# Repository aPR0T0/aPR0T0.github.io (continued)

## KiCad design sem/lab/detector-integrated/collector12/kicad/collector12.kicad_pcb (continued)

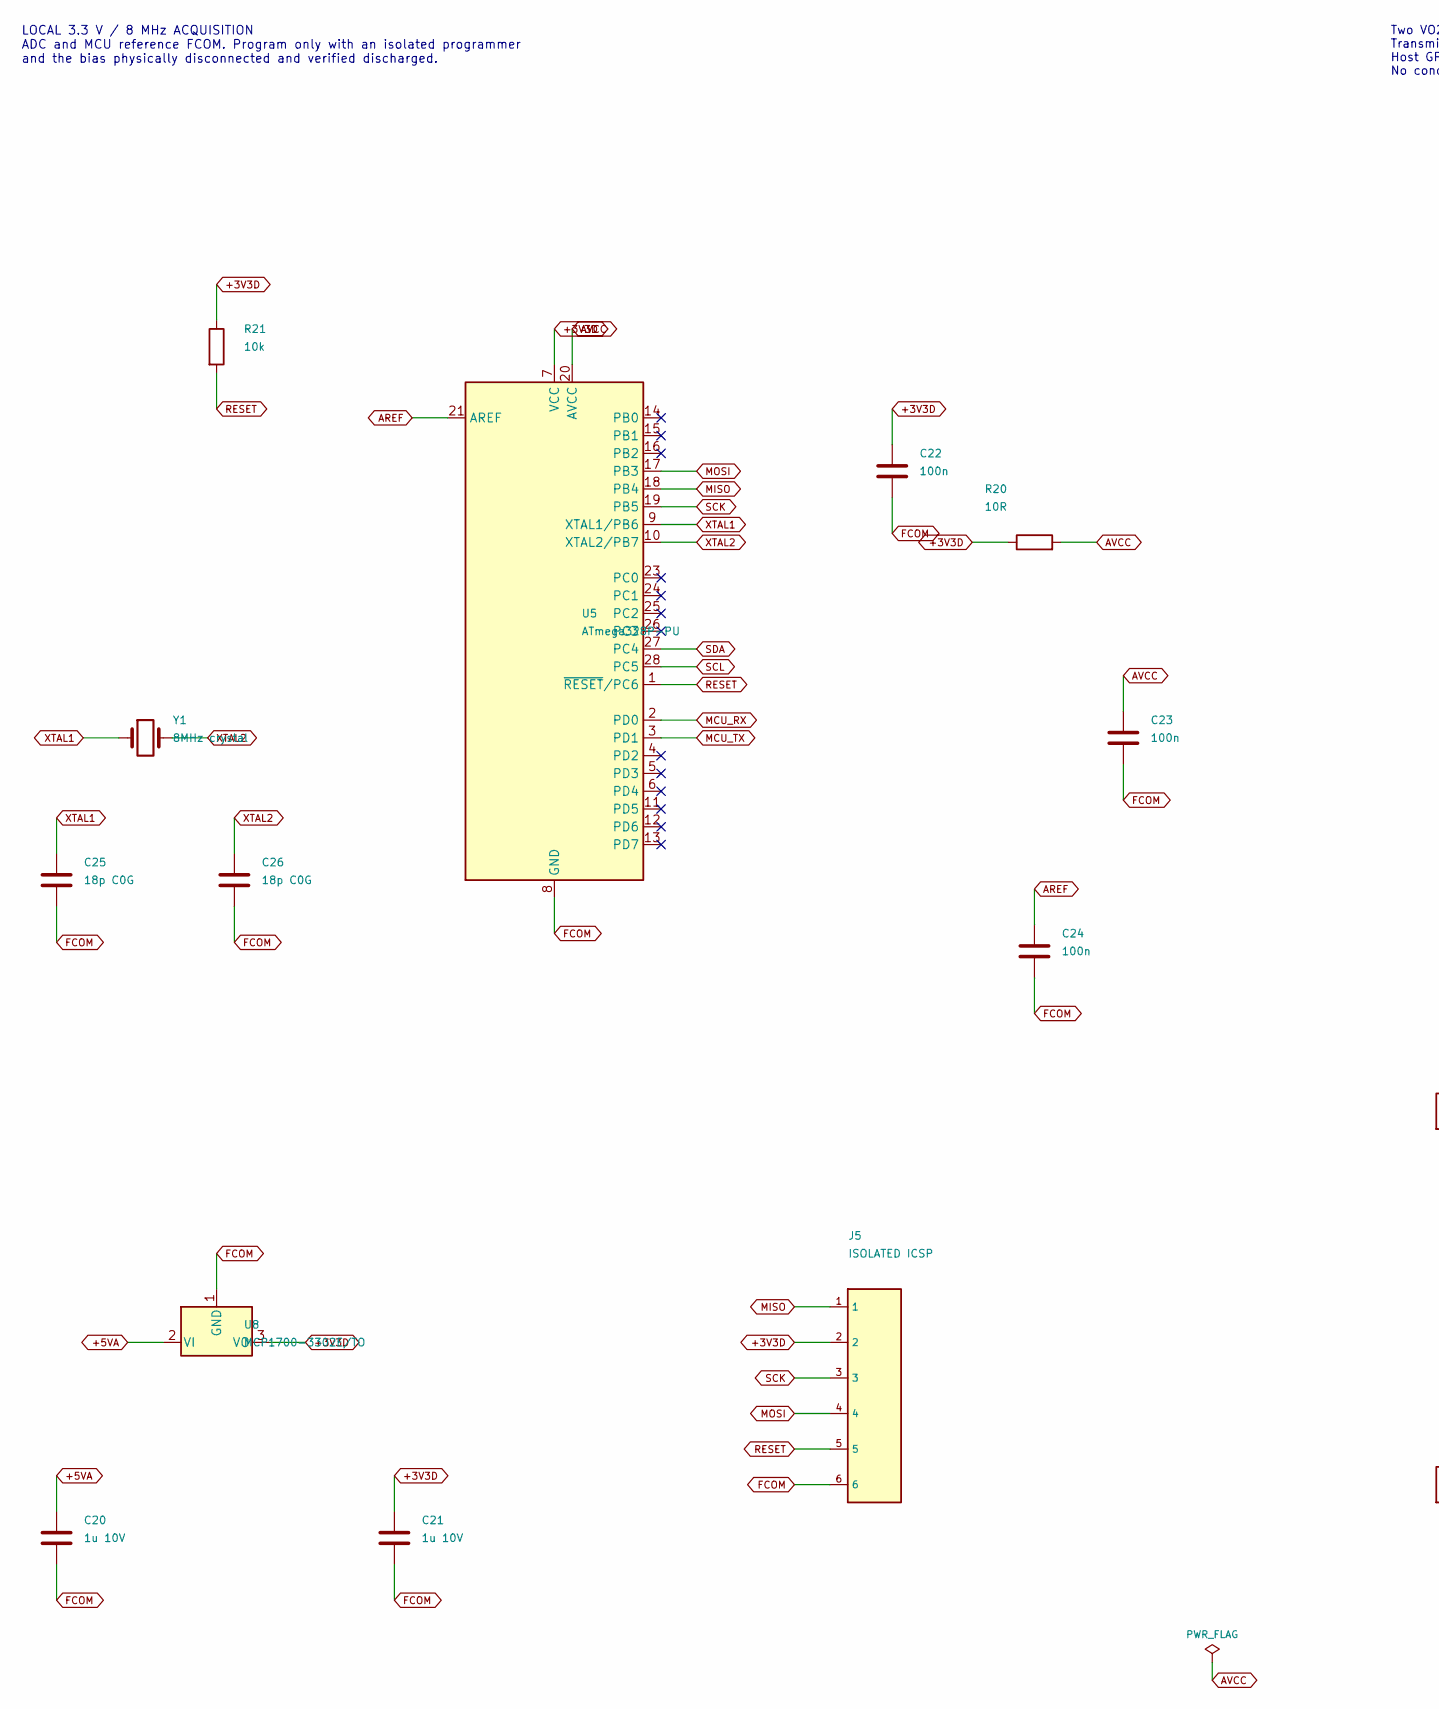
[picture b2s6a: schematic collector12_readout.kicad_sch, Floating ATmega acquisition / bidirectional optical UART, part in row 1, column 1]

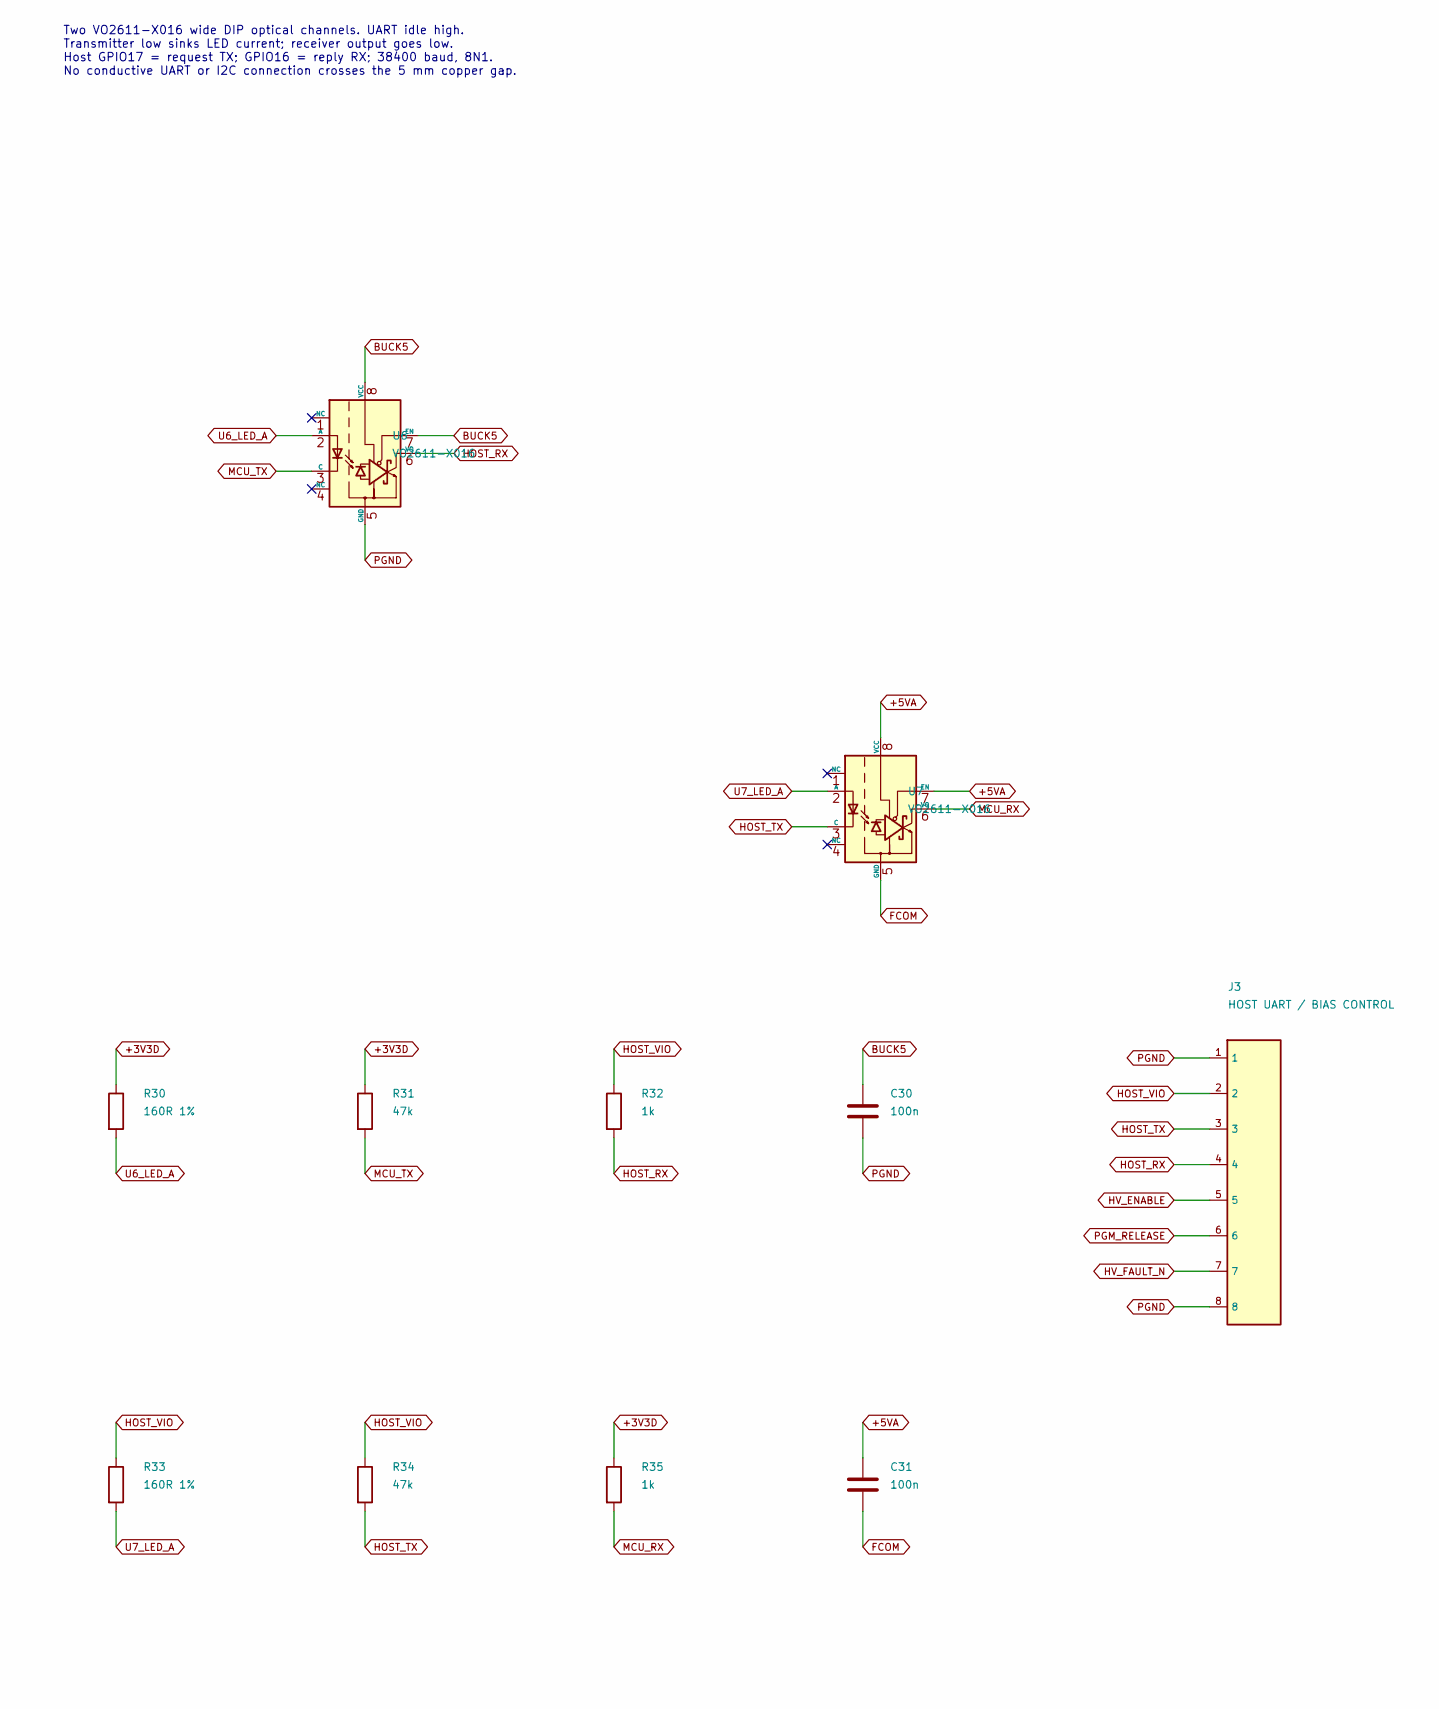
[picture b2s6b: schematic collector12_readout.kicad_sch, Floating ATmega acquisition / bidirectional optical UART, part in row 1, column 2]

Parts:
C20, C21: 1u 10V; C_0805_2012Metric
C22, C23, C24, C30, C31: 100n; C_0805_2012Metric
C25, C26: 18p C0G; C_0805_2012Metric
J3: HOST UART / BIAS CONTROL; PinHeader_1x08_P2.54mm_Vertical
J5: ISOLATED ICSP; PinHeader_2x03_P2.54mm_Vertical
R20: 10R; R_0805_2012Metric
R21: 10k; R_0805_2012Metric
R30, R33: 160R 1%; R_0805_2012Metric
R31, R34: 47k; R_0805_2012Metric
R32, R35: 1k; R_0805_2012Metric
U5: ATmega328P-PU; DIP-28_W7.62mm; MPN ATmega328P-PU
U6, U7: VO2611-X016; DIP-8_W10.16mm; MPN VO2611-X016
U8: MCP1700-3302E/TO; TO-92_Inline; MPN MCP1700-3302E/TO
Y1: 8MHz crystal; Crystal_HC49-U_Vertical

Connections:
+3V3D: C21.1, C22.1, J5.2, R20.1, R21.1, R30.1, R31.1, R35.1, U5.7 (VCC), U8.3 (VO)
+5VA: C20.1, C31.1, U7.7 (EN), U7.8 (VCC), U8.2 (VI); also elsewhere on the board
AREF: C24.1, U5.21 (AREF)
AVCC: C23.1, R20.2, U5.20 (AVCC)
BUCK5: C30.1, U6.7 (EN), U6.8 (VCC); also elsewhere on the board
FCOM: C20.2, C21.2, C22.2, C23.2, C24.2, C25.2, C26.2, C31.2, J5.6, U5.8 (GND), U5.22 (GND), U7.5 (GND), U8.1 (GND); also elsewhere on the board
HOST_RX: J3.4, R32.2, U6.6 (VO)
HOST_TX: J3.3, R34.2, U7.3 (C)
HOST_VIO: J3.2, R32.1, R33.1, R34.1; also elsewhere on the board
HV_ENABLE: J3.5; also elsewhere on the board
HV_FAULT_N: J3.7; also elsewhere on the board
MCU_RX: R35.2, U5.2 (PD0), U7.6 (VO)
MCU_TX: R31.2, U5.3 (PD1), U6.3 (C)
MISO: J5.1, U5.18 (PB4)
MOSI: J5.4, U5.17 (PB3)
PGM_RELEASE: J3.6; also elsewhere on the board
PGND: C30.2, J3.1, J3.8, U6.5 (GND); also elsewhere on the board
RESET: J5.5, R21.2, U5.1 (~RESET/PC6)
SCK: J5.3, U5.19 (PB5)
SCL: U5.28 (PC5); also elsewhere on the board
SDA: U5.27 (PC4); also elsewhere on the board
U6_LED_A: R30.2, U6.2 (A)
U7_LED_A: R33.2, U7.2 (A)
XTAL1: C25.1, U5.9 (XTAL1/PB6), Y1.1
XTAL2: C26.1, U5.10 (XTAL2/PB7), Y1.2

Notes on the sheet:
LOCAL 3.3 V / 8 MHz ACQUISITION ADC and MCU reference FCOM. Program only with an isolated programmer and the bias physically disconnected and verified discharged.
Two VO2611-X016 wide DIP optical channels. UART idle high. Transmitter low sinks LED current; receiver output goes low. Host GPIO17 = request TX; GPIO16 = reply RX; 38400 baud, 8N1. No conductive UART or I2C connection crosses the 5 mm copper gap.

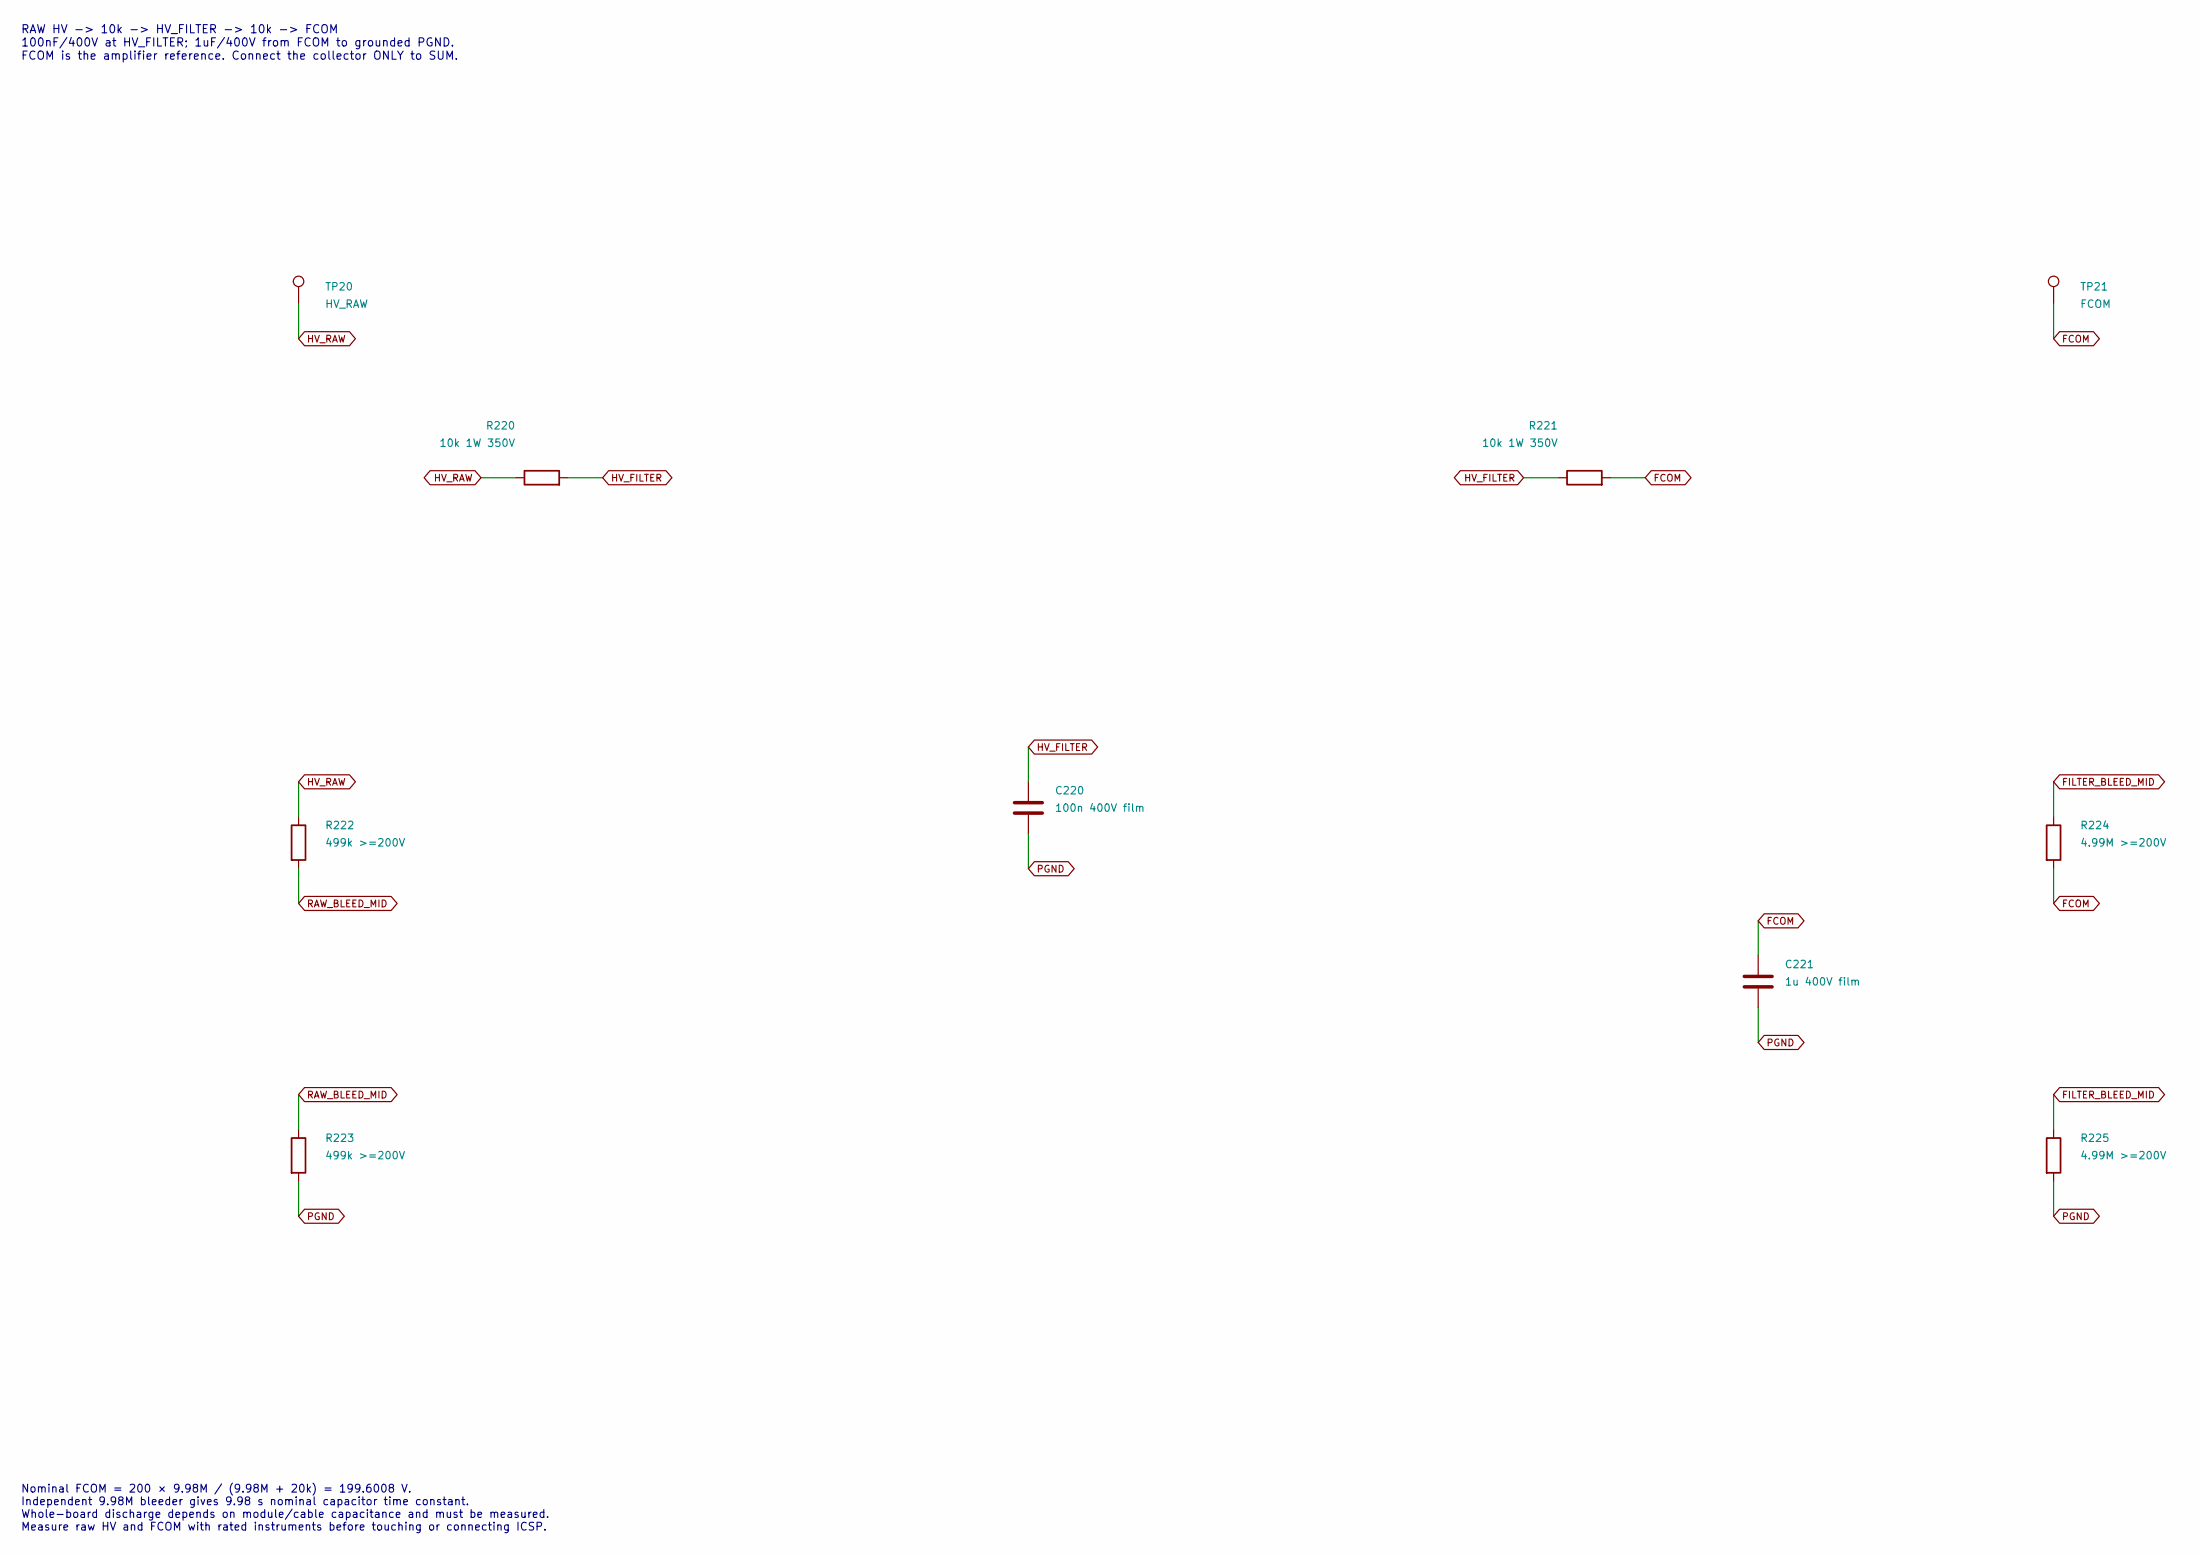
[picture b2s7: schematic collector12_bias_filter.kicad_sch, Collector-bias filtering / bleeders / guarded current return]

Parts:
C220: 100n 400V film; C_Rect_L13.0mm_W5.0mm_P10.00mm_FKS3_FKP3_MKS4
C221: 1u 400V film; C_Rect_L29.0mm_W11.9mm_P27.50mm_MKT
R220, R221: 10k 1W 350V; PR01_P10.16; MPN PR01000101002FA100
R222, R223: 499k >=200V; PR01_P10.16
R224, R225: 4.99M >=200V; PR01_P10.16
TP20: HV_RAW; TestPoint_THTPad_D2.0mm_Drill1.0mm
TP21: FCOM; TestPoint_THTPad_D2.0mm_Drill1.0mm

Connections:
FCOM: C221.1, R221.2, R224.2, TP21.1; also elsewhere on the board
FILTER_BLEED_MID: R224.1, R225.1
HV_FILTER: C220.1, R220.2, R221.1
HV_RAW: R220.1, R222.1, TP20.1; also elsewhere on the board
PGND: C220.2, C221.2, R223.2, R225.2; also elsewhere on the board
RAW_BLEED_MID: R222.2, R223.1

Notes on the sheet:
RAW HV -> 10k -> HV_FILTER -> 10k -> FCOM 100nF/400V at HV_FILTER; 1uF/400V from FCOM to grounded PGND. FCOM is the amplifier reference. Connect the collector ONLY to SUM.
Nominal FCOM = 200 × 9.98M / (9.98M + 20k) = 199.6008 V. Independent 9.98M bleeder gives 9.98 s nominal capacitor time constant. Whole-board discharge depends on module/cable capacitance and must be measured. Measure raw HV and FCOM with rated instruments before touching or connecting ICSP.

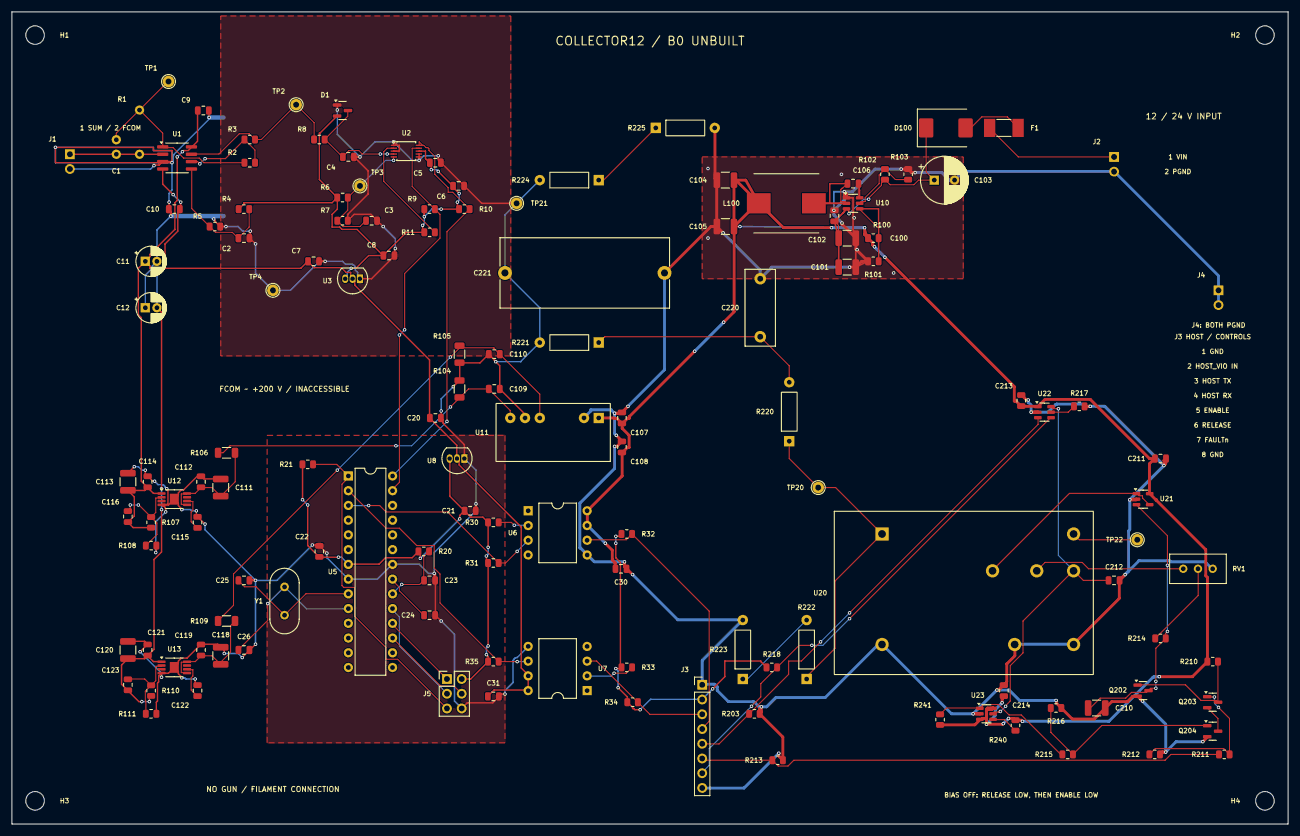
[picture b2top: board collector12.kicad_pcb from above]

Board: 2 copper layers, 220.0 x 140.0 mm, 140 parts (0 on the bottom side), 67 nets.

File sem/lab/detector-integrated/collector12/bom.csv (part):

Reference,Value,Quantity,MPN_or_procurement_spec,Footprint,Function,Datasheet
U1,LMC662AIM,1,LMC662AIMX/NOPB,Package_SO:SOIC-8_3.9x4.9mm_P1.27mm,"Dual CMOS TIA / attenuator; solder directly, no socket",https://www.ti.com/lit/ds/symlink/lmc662.pdf
R1,100M 1%,1,HVA05FA100M,Resistor_THT:R_Axial_DIN0207_L6.3mm_D2.5mm_P7.62mm_Horizontal,100M axial 6x2.5mm body; tolerance calibrates,
C1,10p C0G,1,10p C0G,Capacitor_THT:C_Disc_D3.0mm_W1.6mm_P2.50mm,"TIA stability, tau=1ms nominal; real input capacitance must be tested",
J1,COLLECTOR / FCOM,1,COLLECTOR / FCOM,Connector_PinHeader_2.54mm:PinHeader_1x02_P2.54mm_Vertical,"1 collector, 2 inner guard at FCOM; outer shield to J4 chamber ground",
R2,40.2k 0.1%,1,40.2k 0.1%,Resistor_SMD:R_0805_2012Metric,Attenuator input,
R3,10.0k 0.1%,1,10.0k 0.1%,Resistor_SMD:R_0805_2012Metric,Attenuator feedback,
R4,15.0k 0.1%,1,15.0k 0.1%,Resistor_SMD:R_0805_2012Metric,VBIAS upper divider,
R5,10.0k 0.1%,1,10.0k 0.1%,Resistor_SMD:R_0805_2012Metric,VBIAS lower divider,
C2,1u 10V X7R,1,1u 10V X7R,Capacitor_SMD:C_0805_2012Metric,Quiet 1.32V filter,
R6,1.00k 0.1%,1,1.00k 0.1%,Resistor_SMD:R_0805_2012Metric,ADC midpoint divider upper / rail bleeder,
R7,1.00k 0.1%,1,1.00k 0.1%,Resistor_SMD:R_0805_2012Metric,ADC midpoint divider lower,
C3,10u 10V X7R,1,10u 10V X7R,Capacitor_SMD:C_0805_2012Metric,1.65V reference filter,
R8,820R,1,820R,Resistor_SMD:R_0805_2012Metric,ADC overload current limit; downstream of sensitive node,
C4,100n,1,100n,Capacitor_SMD:C_0805_2012Metric,ADC local RC filter,
D1,BAT54S,1,BAT54S,Package_TO_SOT_SMD:SOT-23,ADC-only Schottky clamp; never on SUM,https://assets.nexperia.com/documents/data-sheet/BAT54S.pdf
U2,ADS1115IDGS,1,ADS1115IDGSR,Package_SO:TSSOP-10_3x3mm_P0.5mm,Differential AIN0-AIN1; I2C0x48; PGA +/-256mV 128SPS defaults,https://www.ti.com/lit/ds/symlink/ads1115.pdf
R9,4.7k,1,4.7k,Resistor_SMD:R_0805_2012Metric,I2C pull-up,
R10,4.7k,1,4.7k,Resistor_SMD:R_0805_2012Metric,I2C pull-up,
R11,10k,1,10k,Resistor_SMD:R_0805_2012Metric,Optional ready open-drain pull-up,
C5,100n,1,100n,Capacitor_SMD:C_0805_2012Metric,ADC local bypass,
C6,1u 10V,1,1u 10V,Capacitor_SMD:C_0805_2012Metric,ADC local bulk bypass,
U3,MCP1700-3302E/TO,1,MCP1700-3302E/TO,Package_TO_SOT_THT:TO-92_Inline,3.3V ADC supply derived from +5V; max input6V,https://www.microchip.com/content/dam/mchp/documents/APID/Pr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
C7,1u 10V,1,1u 10V,Capacitor_SMD:C_0805_2012Metric,LDO input bypass,
C8,1u 10V,1,1u 10V,Capacitor_SMD:C_0805_2012Metric,LDO required output capacitor,
C9,100n,1,100n,Capacitor_SMD:C_0805_2012Metric,LMC positive rail local bypass,
C10,100n,1,100n,Capacitor_SMD:C_0805_2012Metric,LMC negative rail local bypass,
C11,10u 16V,1,10u 16V,Capacitor_THT:CP_Radial_D5.0mm_P2.00mm,Positive rail bulk; positive lead to+5V,
C12,10u 16V,1,10u 16V,Capacitor_THT:CP_Radial_D5.0mm_P2.00mm,Negative rail bulk; positive lead toFCOM,
TP1,TIA,1,TIA,TestPoint:TestPoint_THTPad_D2.0mm_Drill1.0mm,Low impedance measurement only,
TP2,ADC_DRIVE,1,ADC_DRIVE,TestPoint:TestPoint_THTPad_D2.0mm_Drill1.0mm,Low impedance measurement only,
TP3,VMID,1,VMID,TestPoint:TestPoint_THTPad_D2.0mm_Drill1.0mm,Low impedance measurement only,
TP4,FCOM,1,FCOM,TestPoint:TestPoint_THTPad_D2.0mm_Drill1.0mm,Low impedance measurement only,
H1,M3,1,M3,MountingHole:MountingHole_3.2mm_M3,Unplated mounting hole; insulating standoff,
H2,M3,1,M3,MountingHole:MountingHole_3.2mm_M3,Unplated mounting hole; insulating standoff,
H3,M3,1,M3,MountingHole:MountingHole_3.2mm_M3,Unplated mounting hole; insulating standoff,
H4,M3,1,M3,MountingHole:MountingHole_3.2mm_M3,Unplated mounting hole; insulating standoff,
J4,CHAMBER / OUTER SHIELD,1,CHAMBER / OUTER SHIELD,Connector_PinHeader_2.54mm:PinHeader_1x02_P2.54mm_Vertical,"Chamber, enclosure, outer shield; never FCOM",
J2,12/24V DC INPUT,1,12/24V DC INPUT,Connector_PinHeader_2.54mm:PinHeader_1x02_P2.54mm_Vertical,1: positive regulated 9-30 V DC; 2: return. Current-limited source; no mains input.,
F1,1A FAST / 125V,1,0451001.MRL,Fuse:Fuse_Littelfuse-NANO2-451_453,Input wiring/fault fuse; verify converter and input-capacitor inrush against time-current and I-squared-t limits.,https://www.littelfuse.com/products/fuses-overcurrent-protec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
D100,SS36 / 60V,1,SS36-E3/57T,Diode_SMD:D_SMC,"Series reverse-input protection. Pin 1 cathode to protected input; pin 2 anode to fuse. This exact Vishay part is SMC, not SMA.",https://www.vishay.com/docs/88751/ss32.pdf
C100,4.7u 50V,1,4.7u 50V,Capacitor_SMD:C_1210_3225Metric,First buck input capacitor: direct short loop to U10 VIN/GND.,
C101,4.7u 50V,1,4.7u 50V,Capacitor_SMD:C_1210_3225Metric,Second buck input capacitor; total nominal input 9.4 uF.,
C102,100n 50V,1,100n 50V,Capacitor_SMD:C_0805_2012Metric,HF input bypass; shortest possible VIN-to-GND loop.,
C103,22u 50V,1,22u 50V,Capacitor_THT:CP_Radial_D8.0mm_P3.50mm,"22 uF 50 V aluminum, body <=8 mm, leads formed to 3.5 mm pitch; connector-side input bulk. Positive at protected input.",
U10,LMR51420XF,1,LMR51420XFDDCR,Package_TO_SOT_SMD:SOT-23-6,"500 kHz forced-PWM synchronous buck, 4.5-36 V operating. 9-30 V regulated input is the board limit; no automotive surge qualification.",https://www.ti.com/lit/ds/symlink/lmr51420.pdf
L100,10uH / 12A Isat,1,SRP1038A-100M,Integrated:Bourns_SRP1038A,"10 uH, 7.5 A RMS, 12 A Isat, 30 mOhm max. Isat exceeds 5.1 A maximum buck current-limit threshold. Nonpolar.",https://www.bourns.com/docs/product-datasheets/srp1038a.pdf
C104,22u 25V,1,22u 25V,Capacitor_SMD:C_1210_3225Metric,X7R; verify effective capacitance at operating voltage,
C105,22u 25V,1,22u 25V,Capacitor_SMD:C_1210_3225Metric,X7R; verify effective capacitance at operating voltage,
C106,100n 25V,1,100n 25V,Capacitor_SMD:C_0805_2012Metric,Bootstrap capacitor directly between U10 pin 6 CB and pin 2 SW.,
R100,101k 0.1%,1,101k 0.1%,Resistor_SMD:R_0805_2012Metric,Buck feedback top: 0.6*(1+101/13.5) = 5.08889 V nominal. Both divider resistors must be 0.1% to preserve the reviewed module/supervisor voltage margin.,
R101,13.5k 0.1%,1,13.5k 0.1%,Resistor_SMD:R_0805_2012Metric,Buck feedback bottom; Kelvin reference to PGND at input-capacitor return.,
R102,1.00M 1%,1,1.00M 1%,Resistor_SMD:R_0805_2012Metric,"EN divider top: nominal 7.38 V rising UVLO, below accepted 9 V input after series diode.",
R103,200k 1%,1,200k 1%,Resistor_SMD:R_0805_2012Metric,EN divider bottom; about 6.6 V falling UVLO. EN cannot float.,
U11,R05P09D/P,1,R05P09D/P,Integrated:R05P09D_SIP7,"5 V to unregulated +/-9 V, 55 mA each; 1 W. Basic 250 VAC rms working isolation, 4-10 pF; 6.4 kV DC is a 1-second test only. /P gives continuous short protection.",https://www.recom-power.com/pdf/Econoline/RxxPxx.pdf
C107,1u 25V,1,1u 25V,Capacitor_SMD:C_0805_2012Metric,Local primary bypass at the isolation module input pins.,
C108,100n 25V,1,100n 25V,Capacitor_SMD:C_0805_2012Metric,HF primary bypass; does not cross the isolation barrier.,
C109,1u 25V,1,1u 25V,Capacitor_SMD:C_0805_2012Metric,X7R; verify effective capacitance at operating voltage,
C110,1u 25V,1,1u 25V,Capacitor_SMD:C_0805_2012Metric,X7R; verify effective capacitance at operating voltage,
R104,1.30k / 0.25W,1,1.30k / 0.25W,Resistor_SMD:R_1206_3216Metric,Raw positive preload >=6.23 mA at 8.1 V (>10% of 55 mA rail rating).,
R105,1.30k / 0.25W,1,1.30k / 0.25W,Resistor_SMD:R_1206_3216Metric,Raw negative preload. Validate cross-regulation with actual asymmetric load.,
R106,22R / 0.25W,1,22R / 0.25W,Resistor_SMD:R_1206_3216Metric,Series differential ripple filter; 22 ohm with 10 uF gives a 723 Hz nominal pole. Raw preload is before this resistor.,
C111,10u 25V,1,10u 25V,Capacitor_SMD:C_1210_3225Metric,LDO input: actual capacitance >=2.2 uF at bias. 10 uF nominal for AC performance.,
C112,100n 25V,1,100n 25V,Capacitor_SMD:C_0805_2012Metric,X7R; verify effective capacitance at operating voltage,
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
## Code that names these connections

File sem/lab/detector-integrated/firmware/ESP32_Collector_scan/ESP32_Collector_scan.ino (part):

// Integrated collector12 host: classic ESP32-WROOM-32 (noPSRAM).
// Detector J3: 1 PGND, 2 HOST_VIO input from ESP32 3.3V, 3 GPIO17 TX, 4 GPIO16 RX,
// 5 GPIO32 HV_ENABLE, 6 GPIO33 PGM_RELEASE, 7 GPIO34 HV_FAULT_N, 8 PGND.
// Scan GPIO18/23/27; blank GPIO25. FAULT_N requires board pull-up to HOST_VIO.
// LocalATmega ownsADS1115I2C; noI2C/copperbypass acrossFCOMboundary.
// b=enablebiaswithbeamblanked; z=darkzeroatsettledbias; s=start; x=abort/biasoff.
// Set theboardtrimmer onlywhilebeamblanked; measureFCOMwithratedequipment.
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constexpr float CURRENT_GAIN_CORRECTION = 1.000000f;
constexpr uint8_t PIN_LINK_RX = 16;
constexpr uint8_t PIN_LINK_TX = 17;
constexpr uint8_t PIN_HV_ENABLE = 32;
constexpr uint8_t PIN_PGM_RELEASE = 33;
constexpr uint8_t PIN_HV_FAULT_N = 34; // Input-only pin; external 10k pull-up, no internal pull-up.
#if defined(BOARD_HAS_PSRAM)
#error Use an ESP32-WROOM target withoutPSRAM; GPIO16/17are opticalUART.
#endif
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static_assert(SCAN_AMPLITUDE_V >= 0 && SCAN_AMPLITUDE_V <=
  DAC_VREF_V * AMPLIFIER_GAIN * (0.5f - 1.0f/DAC_LEVELS), "DAC range exceeded");
constexpr bool uniqueSignalPins() {
  const uint8_t p[] = {PIN_MOSI,PIN_SCK,PIN_CS,PIN_BLANK,PIN_LINK_RX,PIN_LINK_TX,PIN_HV_ENABLE,PIN_PGM_RELEASE,PIN_HV_FAULT_N};
  for (uint8_t i=0;i<sizeof(p);++i) for (uint8_t j=i+1;j<sizeof(p);++j) if(p[i]==p[j]) return false;
  return true;
}
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uint32_t lastLinkReplyMs=0;
bool faultInputReady=false,hvFaultLatched=false,hvFaultResetting=false;
bool biasRequested=false;
void applyBiasPins(){digitalWrite(PIN_PGM_RELEASE,bias.release?HIGH:LOW);digitalWrite(PIN_HV_ENABLE,bias.power?HIGH:LOW);}
void biasOff(){bias.stop();applyBiasPins();biasRequested=false;calibrated=false;}
bool checkHvFault();

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}

bool checkHvFault() {
  if(!faultInputReady||hvFaultResetting||digitalRead(PIN_HV_FAULT_N)!=LOW)return false;
  if(!hvFaultLatched)detectorFailure("HV power fault latched (overcurrent/reverse/thermal); correct cause, then b to reset and rearm.");
  else {digitalWrite(PIN_BLANK,HIGH);biasOff();armed=false;stopRequested=true;zeroRequested=false;}
  hvFaultLatched=true;
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
bool acquirePixel(int32_t &result) {
  const uint32_t start = micros();
  int32_t sum = 0;
  for (uint8_t i = 0; i < ADC_SAMPLES; ++i) {
    int16_t raw;
    if (!readFreshAdc(raw)) return false;
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  digitalWrite(PIN_BLANK, HIGH);
  // z asserts the blanker; verify the external blanker actually removes beam.
  if (!waitResponsive(SETTLE_US + 50000UL)) { calibrating = false; return; }
  int32_t sum = 0;
  for (uint8_t i = 0; i < 32; ++i) {
    int16_t raw;
    if (!readFreshAdc(raw)) { calibrating = false; return; }
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}

void setup() {
  digitalWrite(PIN_PGM_RELEASE,LOW);pinMode(PIN_PGM_RELEASE,OUTPUT);
  digitalWrite(PIN_HV_ENABLE,LOW);pinMode(PIN_HV_ENABLE,OUTPUT);
  biasOff();
  digitalWrite(PIN_BLANK, HIGH); pinMode(PIN_BLANK, OUTPUT);
  digitalWrite(PIN_CS, HIGH); pinMode(PIN_CS, OUTPUT);
  // No physical LDAC signal for DAC80502; GPIO26 is unused.
  Serial.begin(921600);
  pinMode(PIN_HV_FAULT_N,INPUT);faultInputReady=true;checkHvFault();
  scanSPI.begin(PIN_SCK, -1, PIN_MOSI, PIN_CS);
  collectorSerial.begin(CollectorLink::BAUD,SERIAL_8N1,PIN_LINK_RX,PIN_LINK_TX);
  delay(100); // Allow supply/reference startup while the beam remains blank.
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
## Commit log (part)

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2023-09-29 [Adds email]
2023-11-03 [Initial commit]
2023-11-12 [ Draft ] : Adds images and new page templates
2024-01-03 [ Profile Update ] : Adds Domains and updates banner
2024-06-23 [ Updates ] : Profile Updates and adds some projects without pictures
2024-06-24 [ Updates ] : Removes blogs section
2024-06-24 [ Fixes ] : Mobile Menu mail and log fixes
2024-06-24 [ Minor Fixes ] : Toggle button visibility fix
2024-06-27 [ Blog#1 ] : EvoBorne
2024-06-29 [ Blog ] [ June 28th 2024 ] : Adds The first look of the monster
2024-09-13 [ Acti-V-link Blog ][ Gallery ] : Adds new blog 13/09/2024 and some images
2024-09-13 [ Minor Update ] : Fit content issues on the Acti-V-Link Blog
2024-09-27 [ Anuvadak Blog ][ Gallery ] : Adds new blog and working of Anuvadak to the gallery
2024-10-08 [ Publications ] : Adds Publications
2026-06-15 [ Briefings ] : Converts mission pages to tactical dossiers
2026-06-15 [ Fix ] : Resolve project assets via import.meta.glob so gallery images build
2026-06-15 [ Hero ] : Photoreal Pandora hero with CC0 HDRI + photoscanned floating islands
    - Replace procedural islands/sky with real CC0 Poly Haven assets (meshopt+WebP .glb)
    - HDRI image-based lighting + sky, ACES tone mapping, soft shadows
    - Post-processing: GTAO, UnrealBloom, depth of field, SMAA
    - Time-based hero reveal (frame-rate independent)
    - Add favicon link
2026-06-15 [ Studio ] : COD/GTA-grade studio — PBR concrete, IBL, shadows, post FX
    - ACES tone mapping + PCFSoft shadows + RoomEnvironment image-based lighting
    - CC0 Poly Haven PBR concrete floor/walls (2k diff/normal/arm), metal trim
    - Shadow casting/receiving on operative, frames, pedestal, sculpture
    - Post-processing: GTAO, UnrealBloom, film grain + vignette + chromatic aberration, SMAA
    - Physically-based light intensities; favicon link
2026-06-16 [ Pandora ] : Nightfall world, fonts, multiplayer, studio glass room + emotes
    Fonts
    - Pixelify Sans display + slot-machine name reveal on the hero
    - Unify all pages to Pixelify (headings) + Chakra Petch (body)
    Night Pandora hero
    - CC0 night HDRI, moonlight + night fog/exposure, night CSS retheme
    - Procedural bioluminescence: glowing flora, spores, woodsprites, fireflies
2026-06-16 [ Multiplayer ] : Wire live Supabase Realtime keys (publishable)
2026-06-16 [ Hero ] : Replace Pandora islands with a sunny cloudscape flight
    - Volumetric raymarched cloud deck (fullscreen shader) — a view from a
    plane flying forward through sunlit clouds
    - Subtle cursor-steered heading + gentle banking; smooth, understated
    - Bright sky retheme of the hero (dark readable text scoped to .hero;
    map + uplink stay dark for the descend-into-the-tactical-world flow)
    - Drop the night HDRI / GLTF / GTAO / Bokeh / SMAA usage from the landing
2026-06-16 [ Hero ] : Bluer sky, fuller self-shadowed clouds, glassy 3D name
    - Remove the sun from the scene; deeper, visibly-blue sky gradient
    - Denser cloud deck with light-march self-shadowing (Beer's law + powder)
    for real depth and 3D structure
    - Frosted liquid-glass panel behind the hero copy with beveled, glassy
    3D lettering; glassy enter button
2026-06-16 [ Hero ] : True 3D glass name + clearer sky with sparse clouds
    - Hero name rendered as real transmissive 3D glass (MeshPhysicalMaterial
    TextGeometry, optimer serif) with IBL + key/rim lights, bevels, refraction
    and a soft eased reveal + gentle cursor-tilt parallax
    - HTML <h1> kept (hidden) for layout + accessibility; glass text auto-fits
    and re-lays out on resize
    - Clouds: sparser, bolder puffs over a clearer, brighter blue sky
2026-06-16 [ Hero/Links ] : Bolder modern glass name, dispatch comms, fixed links
    - Glass name: switch to a modern sans (helvetiker), much stronger glass
    (thicker tinted body, iridescence, higher reflectivity/env, brighter
    key/rim/fill lights + more bloom) so it reads clearly
    - Landing page: add a military TRANSMIT DISPATCH comms form (EmailJS) in
    the uplink section with console-style feedback
    - Fix old-website links across blogs/publications/contact: dead logo '#'
2026-06-16 [ Hero ] : Lightweight landing — defer supabase, lazy EmailJS, lower GPU cost
    - Multiplayer/Supabase (~45KB gz) now loads only when the recon map is
    scrolled into view (not on initial landing load) + no websocket on boot
    - EmailJS loaded on demand (removed the render-blocking <head> script)
    - Cap hero DPR (1.5 desktop / 1 mobile), fewer cloud raymarch steps, and
    lighter glass text geometry — same look, far less per-pixel/GPU work
2026-06-16 [ Studio/Comms ] : Beautiful animated robot avatar + email backup relay
    - Add RobotExpressive (CC0) — a beautiful, fully-rigged + animated character
    selectable in the studio (press V / avatar button) and rendered for remote
    players too; instanced via SkeletonUtils with its own mixer (idle/walk/run)
    + procedural jump/emotes; added to the random avatar roster
    - Comms: on EmailJS failure (e.g. Gmail invalid_grant) both the landing
    dispatch and the contact console now fall back to a prefilled mailto
2026-06-16 [ Studio ] : Real-animation characters — proper scale, clip-driven moves, skins
    - Replace soldier + procedural capsules with the high-fidelity rigged
    RobotExpressive (CC0) at correct human scale (was tiny)
    - ALL moves are now REAL animation clips (not transforms): Walk/Run/Idle
    locomotion crossfades + Jump/Dance/Wave/Punch/ThumbsUp/Yes/No emotes,
    synced to peers via an emote-edge counter
    - Six colour skins (V / avatar button) for variety; remotes render the
2026-06-16 [ Studio ] : Multiple big high-fidelity characters with real animations
    - 6 distinct characters: KayKit Adventurers (Knight, Barbarian, Mage,
    Rogue, Assassin — CC0) + RobotExpressive, cycle with V / avatar button
    - All driven by REAL animation clips per character (shared 76-clip KayKit
    rig + robot's own set): walk/run/idle + jump/wave/dance/punch/kick/spin/cheer
    - Characters scaled much larger (CHAR_HEIGHT 5.0, was ~1.95) with camera
    pulled back + raised to frame them; lazy-loaded + cached per character
2026-06-16 [ Studio/Hero ] : Combat — life bars, real fighting moves, win-to-advance
    - Landing: 3D glass name more opaque (0.93)
    - Characters now have LIFE (HP) with on-screen vitals bar + floating HP
    bars over remote operatives
    - More fighting moves, all REAL clips: punch/kick/slash/chop/stab/spin
    (Q/C/X/E/R/B) with frontal-arc hit detection + impact sparks
    - Hits damage peers over the realtime channel; 0 HP = downed (death anim)
2026-06-16 [ Studio ] : Kill-feed + scoreboard, lock-on targeting, VICTOR banner
    - Kill feed: live KO lines (KILLER ⚔ VICTIM), your own highlighted
    - Scoreboard: per-operative knockout tally (top 6), shown in multiplayer
    - Lock-on (TAB): cycle targets, spinning reticle with name+HP projected
    over the locked operative; player auto-faces the target when stationary
    - Banner: big VICTOR on a knockout, DOWNED when you fall
2026-06-16 [ Studio ] : Over-head HP bars (incl. local, moving) + flip move
    - HP bar + callsign now float above EVERY character's head and move with
    them — including your own local character
    - New FLIP move (Z): real jump clip + a centred 360 somersault (pivot at
    the character's centre), synced to peers
2026-06-16 [ Studio ] : Flip = evasive dodge (i-frames) + double-jump
    - Flip (Z) now grants ~0.65s invulnerability — incoming hits during the
    flip whiff ('DODGED'), with a cyan EVADE cue on the vitals bar; 1s
    cooldown prevents i-frame spam
    - Double-jump: tap SPACE again in mid-air for a second jump that performs
    an aerial flip-dodge
2026-06-16 [ Studio/Hero ] : Brighter exterior vista + glass-themed hero text
    - Studio: lift the night world outside the glass — brighter HDRI sky,
    lighter fog, stronger moonlight + hemisphere fill, bigger gas giant,
    punchier bioluminescent flora
    - Landing: eyebrow, role, ENTER button and DESCEND cue restyled as frosted
    glass chips (blur + light border + inset highlight) to match the 3D
    glass name
2026-06-16 [ Studio ] : Swap exterior to a sunny cloud sky (like the landing)
    - Replace the night Pandora vista (HDRI + gas giant/moon/bioluminescent
    flora/fireflies) with a daytime cloud SKYDOME shader: blue sky gradient,
    drifting FBM clouds, soft sun + a cloud sea below the tower
    - Daytime lighting (sun + sky hemisphere), generated sky-gradient IBL for
    bright glass reflections, light blue haze
    - Drifting cloud billboards outside the glass for parallax depth
2026-06-16 [ Studio ] : PSP-style mobile controls (landscape)
    - On-screen gamepad for touch + landscape: left analog nub, upper-left
    d-pad (wave/dance/cheer/swap), right face diamond (X jump, square punch,
    O kick, triangle flip), L lock-on / R slash shoulders, START/SELECT room nav
    - Glassy PSP styling with safe-area insets + haptic tap feedback
    - Camera look reworked to a single-pointer right-side zone (no longer
    fights the stick/buttons); multi-touch via per-control pointer capture
2026-06-16 [ Landing ] : Split WebGL hero into desktop-only lazy chunk; pure-CSS mobile landing
    - Extract cloud + 3D glass-name hero to assets/js/hero3d.js (initHero3d)
    - Desktop: dynamic-import hero3d (three loads lazily) + interactive map
    - Mobile/touch: skip three entirely, render lightweight CSS sky + project cards
    - Share channels/year/ticker/dispatch across both layouts
2026-06-16 [ Landing ] : Slot-machine "juggle" name reveal on desktop + mobile
    - Add shared assets/js/nameSlot.js (buildSlots + runSlots)
    - Desktop: HTML hero name juggles in, then crystallises into the 3D glass (fade-driven)
    - Mobile: lazy-load nameSlot and juggle the CSS landing name
    - Respect prefers-reduced-motion (snap to locked)
2026-06-17 [ Landing ] : Liquid-glass refresh + juggle title; readable blog theme & toggle; prune pages
    Landing:
    - Replace slot-machine reveal with a toss-&-catch juggle (word-aware, reduced-motion safe)
    - Title-case 'Mohd Alqama Shaikh' in Sora; drop the WebGL 3D glass name (keep cloud bg) so the name stays crisp
    - Reusable Liquid-Glass system (deeper frost + specular rim + sheen, @supports fallback, grain) across hero/chips/dossier/channels/uplink
    - Mobile: boxy-but-glassy hero card, volumetric clouds + aurora, roomier spacing
    Blogs:
2026-06-30 [ Site ] : Use classic scripts instead of ES modules so images/terminal render under file:// too
    ES modules are blocked under file://, leaving the terminal (and its images)
    blank when index.html is opened directly. Switch content.js/app.js to classic
    scripts sharing global scope; load content first. Works over http and offline.
2026-06-30 [ Site ] : Add blogs page + first post; add world-system motive to about
    - New ./blogs index and ./blogs/<slug> post routing (nav, ls, tab-complete)
    - First post: 'In Search of a Better System to Run the World'
    - about + tagline now state the two motives: no one sleeps hungry,
    and no one sleeps without a smile
2026-06-30 [ Blog ] : Password-gated in-browser editor that commits to GitHub (WebCrypto)
    - Move posts to posts.js (window.BLOG_POSTS) so the editor can rewrite 1 file
    - author.js: AES-256-GCM + PBKDF2 (600k) encrypt of a GitHub token with your
    password; login decrypts it (wrong password = AES auth-tag fail, no hash kept)
    - Commands: auth setup/status/publish/reset, login, logout, edit <slug>, new
    - Inline editor commits posts.js via GitHub Contents API; Pages redeploys
    - extraCommands registry hook in app.js; editor/auth CSS; README security notes
2026-06-30 [ Blog ] : Fix auth prompts auto-cancelling — Enter that launches a prompt no longer submits its empty field
    The Enter used to run 'auth setup'/'login' bled through to the freshly-focused
    inline prompt and implicitly submitted it empty, reading as cancelled. Defer the
    prompt's focus and 'arm' it on a later tick, and ignore Enter/submit until armed.
    Also defer the editor's initial focus for the same reason.
2026-06-30 blog: edit a-better-system-to-run-the-world
